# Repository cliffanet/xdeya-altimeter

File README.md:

# Высотомер "Хде-Йа"

Инструмент для парашютиста - гибрид высотомера и Navi-возвращалки.

***
## Возможности

* Классические для высотомера: отображение высоты, логбук и т.д.
* Приём сигнала навигации (GPS + GLONASS)
* Отображение направления и расстояния до заранее сохранённой точки (возвращалка)
* Отображение вертикальной (по барометру) и горизонтальной (по навигации) скоростей
* В логбуке сохраняются показания высотомера и координаты на местности
* Запись трека со всеми имеющимися параметрами барометра и GPS/GLONASS-приёмника
* Взаимодействие с приложением (просмотр логбука, прыжков)

***
## Назначение

* Изначально устройство разрабатывалось как возвращалка в плохих метеоусловиях.

* Студенты, тренирующие точность приземления, смогут на земле разобрать прыжок, имея объективное средство контроля своих перемещений в пространстве.

* Мне как лот организатору групповых прыжков помогало контролировать точку выброски, сильно разгружая голову для остальных функций (взаимодействие с подопечными на борту, дополнительный контроль верности сигналов на выброску), а также помогая объективно оценить задержки выброски из-за неуспевания подготовиться вовремя к отделению.

* Инженеры, программисты микроконтроллеров, использующих Arduino и подобные средства разработки, найдут в этом устройстве полигон для экспериментов в воздухе.

>**Важно:** Устройство не может использоваться для тайного контроля за владельцем, т.к. передача данных вне устройства происходит только по запросу пользователя.

Впрочем, это открытый проект, и каждый может доработать Программное Обеспечение под свои нужды.

***
## Документация

* [Самое краткое руководство](doc/userman/simple/README.md) \[[PDF](doc/userman/xdeya-simple.pdf)|[Word](doc/userman/xdeya-simple.docx)\]
* [Как это сделать?](doc/userman/howdo/README.md) \[[PDF](doc/userman/xdeya-howdo.pdf)|[Word](doc/userman/xdeya-howdo.docx)\]
* [Описание Меню прибора](doc/userman/menu/README.md) \[[PDF](doc/userman/xdeya-menu.pdf)|[Word](doc/userman/xdeya-menu.docx)\]
* [Технические особенности и разъяснения](doc/userman/tech/README.md) \[[PDF](doc/userman/xdeya-tech.pdf)|[Word](doc/userman/xdeya-tech.docx)\]

* [Модификации](doc/models/README.md) - подробное описание аппаратных вариантов и их особенностей с фото.
* [Используемые комплектующие](doc/build/hardware.md)
* [Сколько стоит и где купить](doc/build/price.md)
* [Исходники](doc/code/README.md) - где, что лежит, права на использование, помощь при компиляции.
* [Где скачать](doc/download.md)

***

<video width="475" controls title="demo">
  <source src="doc/demo.mp4" type="video/mp4">
</video>

***
## Контакты

Меня зовут Николай, веду проект `Высотомер + Навигация`. Связаться со мной можно:

* Telegram канал с информацией: [@xdeya](https://t.me/xdeya)
* Telegram: [Cliff](https://t.me/cliffa_net)
* cliff_mail@mail.ru
* Cайт проекта: [xdeya.ru](http://xdeya.ru)

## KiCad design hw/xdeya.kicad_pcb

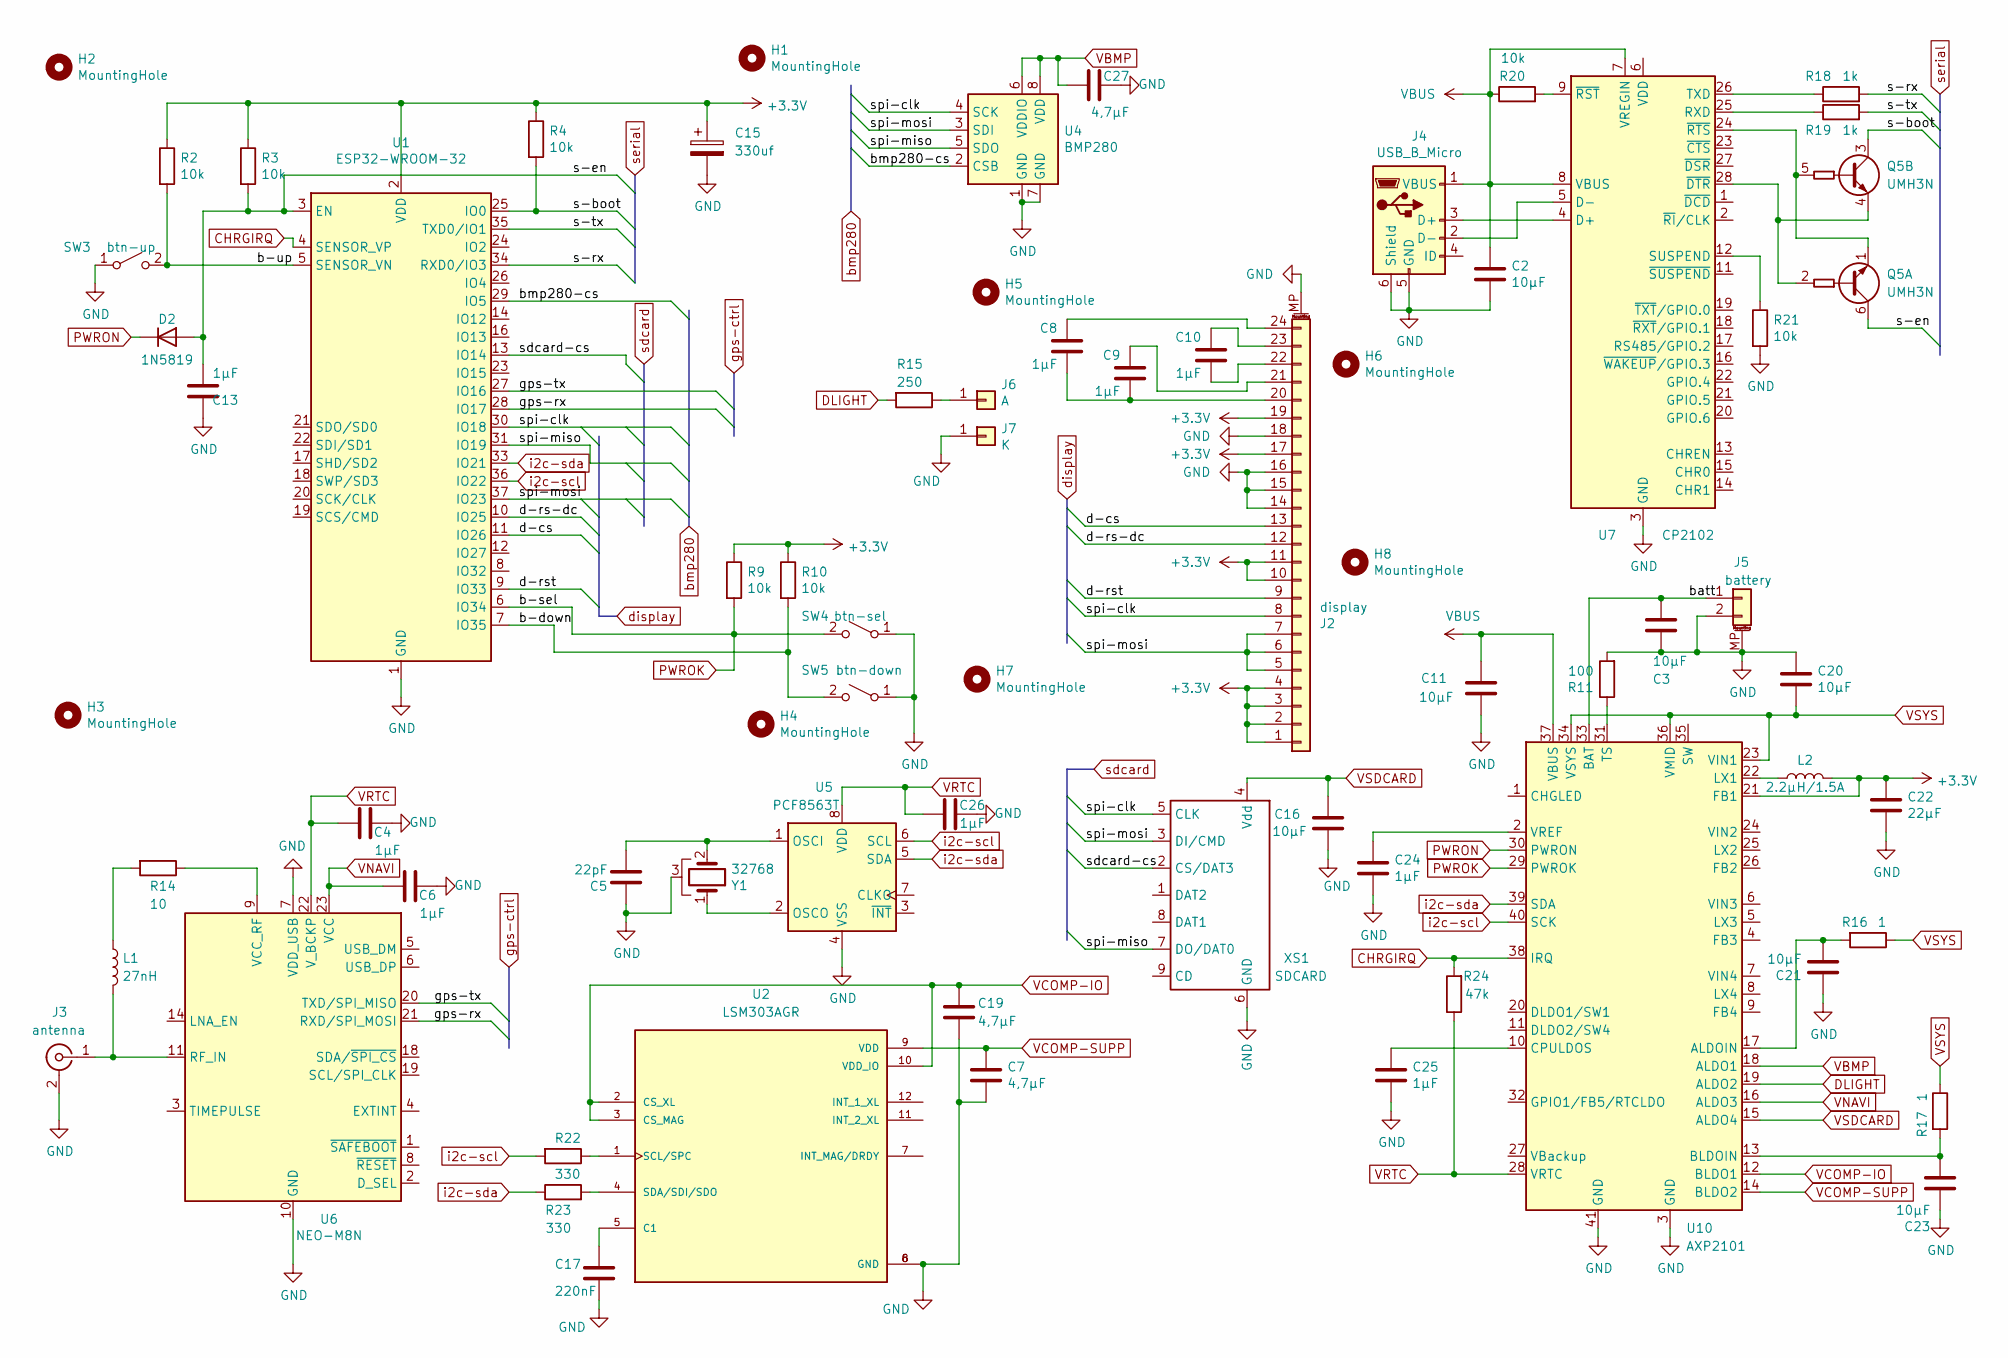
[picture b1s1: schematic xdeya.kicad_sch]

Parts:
C2, C3, C11, C16, C20, C21, C23: 10μF; C_0805_2012Metric
C4, C6, C8, C9, C10, C13, C24, C25, C26: 1μF; C_0805_2012Metric
C5: 22pF; C_0805_2012Metric
C7, C19, C27: 4,7μF; C_0805_2012Metric
C15: 330uf; CP_EIA-7343-20_Kemet-V
C17: 220nF; C_0805_2012Metric
C22: 22μF; C_0805_2012Metric
D2: 1N5819; D_SOD-323
H1, H2, H3, H4: MountingHole; MountingHole_3.2mm_M3
H5, H6: MountingHole; MountingHole_2.2mm_M2
H7, H8: MountingHole; MountingHole_1.5
J2: display; TE_2-1734839-4_1x24-1MP_P0.5mm_Horizontal
J3: antenna; SMA_Molex_73251-2200_Horizontal
J4: USB_B_Micro; USB_Micro-B_Molex-105017-0001
J5: battery; Molex_PicoBlade_53261-0271_1x02-1MP_P1.25mm_Horizontal
J6: A; SolderWire-1sqmm_1x01_D1.4mm_OD2.7mm
J7: K; SolderWire-1sqmm_1x01_D1.4mm_OD2.7mm
L1: 27nH; L_0805_2012Metric
L2: 2.2μH/1.5A; L_Wurth_WE-LQSH-3012
Q5: UMH3N; SOT-363_SC-70-6
R2, R3, R4, R9, R10, R20, R21: 10k; R_0805_2012Metric
R11: 100; R_0805_2012Metric
R14: 10; R_0805_2012Metric
R15: 250; R_0805_2012Metric
R16, R17: 1; R_0805_2012Metric
R18, R19: 1k; R_0805_2012Metric
R22, R23: 330; R_0805_2012Metric
R24: 47k; R_0805_2012Metric
SW3: btn-up; SW_Push_1P1T_NO_6x6mm_H9.5mm
SW4: btn-sel; SW_Push_1P1T_NO_6x6mm_H9.5mm
SW5: btn-down; SW_Push_1P1T_NO_6x6mm_H9.5mm
U1: ESP32-WROOM-32
U2: LSM303AGR; PQFN50P200X200X100-12N; PARTREV 10
U4: BMP280; Bosch_LGA-8_2x2.5mm_P0.65mm_ClockwisePinNumbering
U5: PCF8563T; SOIC-8_3.9x4.9mm_P1.27mm
U6: NEO-M8N; ublox_NEO
U7: CP2102; QFN-28-1EP_5x5mm_P0.5mm_EP3.35x3.35mm
U10: AXP2101; QFN-40-1EP_5x5mm_P0.4mm_EP3.6x3.6mm_ThermalVias
XS1: SDCARD; Conn_uSDcard
Y1: 32768; Crystal_DS26_D2.0mm_L6.0mm_Horizontal_1EP_style2

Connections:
+3.3V: C15.1, C22.1, J2.1, J2.2, J2.3, J2.4, J2.10, J2.11, J2.17, J2.19, L2.2, R2.1, R3.1, R4.1, R9.1, R10.1, U1.2 (VDD), U10.21 (FB1)
/b-down: R10.2, SW5.2 (B), U1.7 (IO35)
/b-up: R2.2, SW3.2 (B), U1.5 (SENSOR_VN)
/batt: C3.1, J5.1, U10.33 (BAT)
/bmp280-cs: U1.29 (IO5), U4.2 (CSB)
/d-cs: J2.13, U1.11 (IO26)
/d-rs-dc: J2.12, U1.10 (IO25)
/d-rst: J2.9, U1.9 (IO33)
/gps-rx: U1.28 (IO17), U6.21 (RXD/SPI_MOSI)
/gps-tx: U1.27 (IO16), U6.20 (TXD/SPI_MISO)
/s-boot: Q5.3 (C2), R4.2, U1.25 (IO0)
/s-en: C13.2, D2.2 (A), Q5.6 (C1), R3.2, U1.3 (EN)
/s-rx: R18.2, U1.34 (RXD0/IO3)
/s-tx: R19.2, U1.35 (TXD0/IO1)
/sdcard-cs: U1.13 (IO14), XS1.2 (CS/DAT3)
/spi-clk: J2.8, U1.30 (IO18), U4.4 (SCK), XS1.5 (CLK)
/spi-miso: U1.31 (IO19), U4.5 (SDO), XS1.7 (DO/DAT0)
/spi-mosi: J2.5, J2.6, J2.7, U1.37 (IO23), U4.3 (SDI), XS1.3 (DI/CMD)
CHRGIRQ: R24.2, U1.4 (SENSOR_VP), U10.38 (IRQ)
DLIGHT: R15.2, U10.19 (ALDO2)
GND: C2.2, C3.2, C4.2, C5.1, C6.2, C7.2, C11.1, C13.1, C15.2, C16.2, C17.2, C19.2, C20.1, C21.1, C22.2, C23.1, C24.2, C25.2, C26.2, C27.2, J2.14, J2.15, J2.16, J2.18, J2.MP (MountPin), J3.2 (Ext), J4.5 (GND), J4.6 (Shield), J5.2, J5.MP (MountPin), J7.1, R11.2, R21.2, SW3.1 (A), SW4.1 (A), SW5.1 (A), U1.1 (GND), U1.15 (GND), U1.38 (GND), U1.39 (GND), U2.6 (GND), U2.8 (GND), U4.1 (GND), U4.7 (GND), U5.4 (VSS), U6.7 (VDD_USB), U6.10 (GND), U6.12 (GND), U6.13 (GND), U6.24 (GND), U7.3 (GND), U7.29 (GND), U10.3 (GND), U10.41 (GND), XS1.6 (GND), Y1.3
unnamed: C8.1, C9.1, J2.20
unnamed: C9.2, J2.21
unnamed: C10.1, J2.22
unnamed: C10.2, J2.23
unnamed: C8.2, J2.24
unnamed: J3.1 (In), L1.2, U6.11 (RF_IN)
unnamed: J4.3 (D+), U7.4 (D+)
unnamed: J4.2 (D-), U7.5 (D-)
unnamed: J6.1, R15.1
unnamed: L1.1, R14.2
unnamed: Q5.2 (B1), Q5.4 (E2), U7.28 (~DTR)
unnamed: Q5.1 (E1), Q5.5 (B2), U7.24 (~RTS)
unnamed: C17.1, U2.5 (C1)
unnamed: R22.1, U2.1 (SCL/SPC)
unnamed: R23.2, U2.4 (SDA/SDI/SDO)
unnamed: C5.2, U5.1 (OSCI), Y1.2
unnamed: U5.2 (OSCO), Y1.1
unnamed: R14.1, U6.9 (VCC_RF)
unnamed: R19.1, U7.25 (RXD)
unnamed: R21.1, U7.12 (SUSPEND)
unnamed: R18.1, U7.26 (TXD)
unnamed: R20.2, U7.9 (~RST)
unnamed: C21.2, R16.2, U10.17 (ALDOIN)
unnamed: C23.2, R17.2, U10.13 (BLDOIN)
unnamed: C25.1, U10.10 (CPULDOS)
unnamed: L2.1, U10.22 (LX1)
unnamed: R11.1, U10.31 (TS)
unnamed: C24.1, U10.2 (VREF)
PWROK: R9.2, SW4.2 (B), U1.6 (IO34), U10.29 (PWROK)
PWRON: D2.1 (K), U10.30 (PWRON)
VBMP: C27.1, U4.6 (VDDIO), U4.8 (VDD), U10.18 (ALDO1)
VBUS: C2.1, C11.2, J4.1 (VBUS), R20.1, U7.7 (VREGIN), U7.8 (VBUS), U10.37 (VBUS)
VCOMP-IO: C19.1, U2.2 (CS_XL), U2.3 (CS_MAG), U2.10 (VDD_IO), U10.12 (BLDO1)
VCOMP-SUPP: C7.1, U2.9 (VDD), U10.14 (BLDO2)
VNAVI: C6.1, U6.23 (VCC), U10.16 (ALDO3)
VRTC: C4.1, C26.1, R24.1, U5.8 (VDD), U6.22 (V_BCKP), U10.28 (VRTC)
VSDCARD: C16.1, U10.15 (ALDO4), XS1.4 (Vdd)
VSYS: C20.2, R16.1, R17.1, U10.23 (VIN1), U10.34 (VSYS), U10.36 (VMID)
i2c-scl: R22.2, U1.36 (IO22), U5.6 (SCL), U10.40 (SCK)
i2c-sda: R23.1, U1.33 (IO21), U5.5 (SDA), U10.39 (SDA)

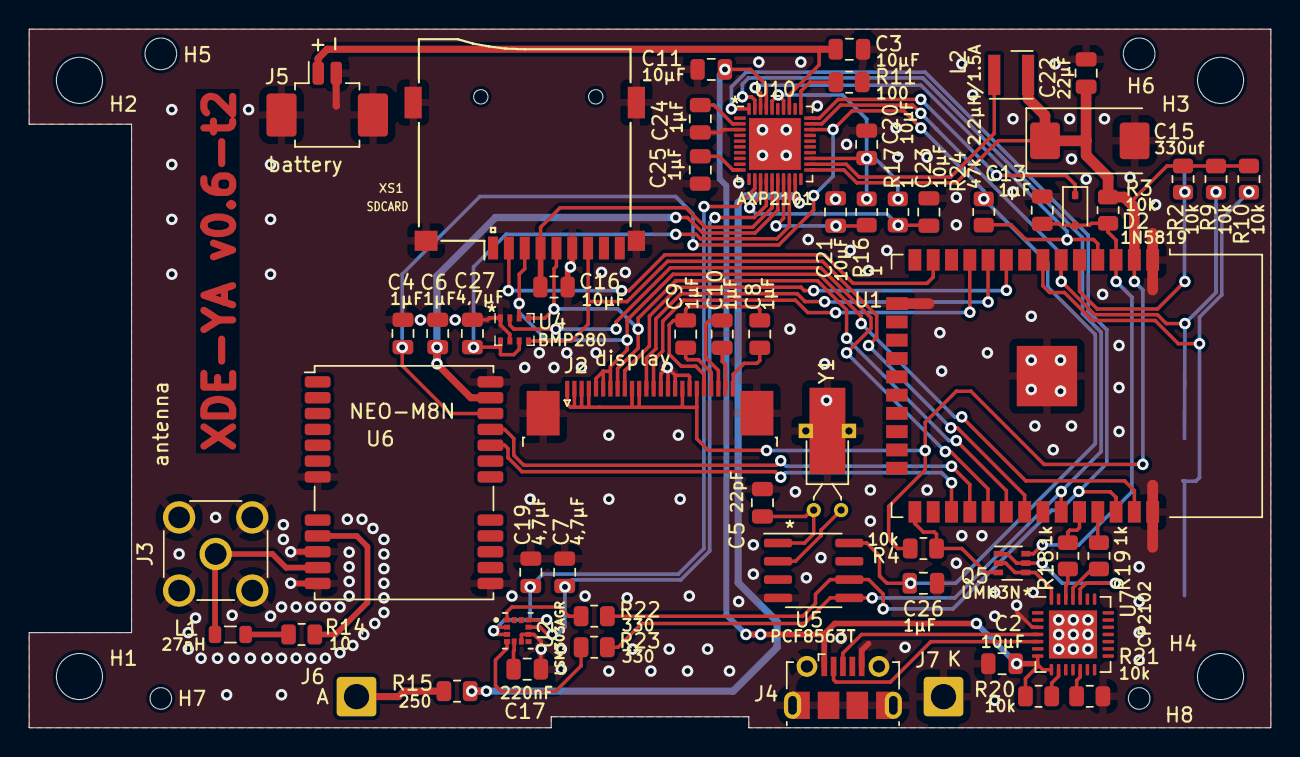
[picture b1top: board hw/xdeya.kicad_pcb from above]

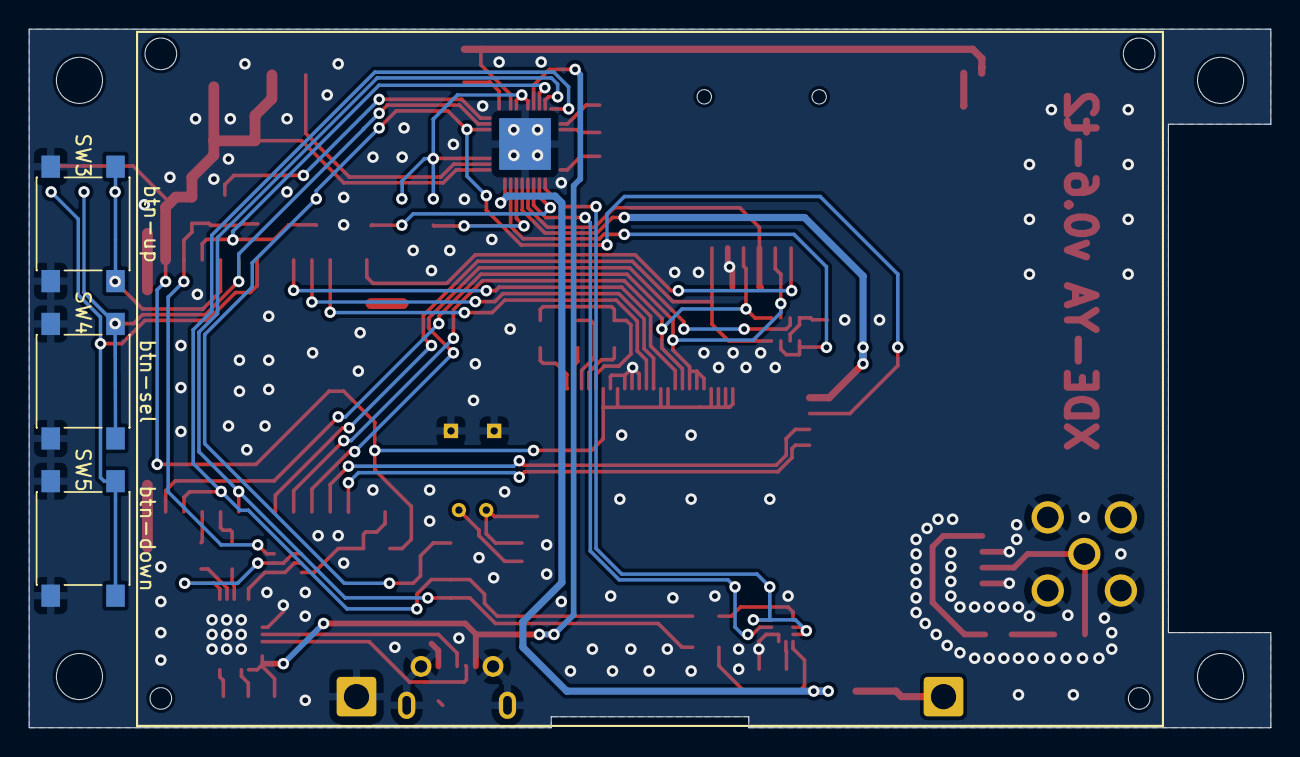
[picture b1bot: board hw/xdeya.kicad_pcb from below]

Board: 2 copper layers, 86.2 x 48.5 mm, 70 parts (3 on the bottom side), 61 nets.

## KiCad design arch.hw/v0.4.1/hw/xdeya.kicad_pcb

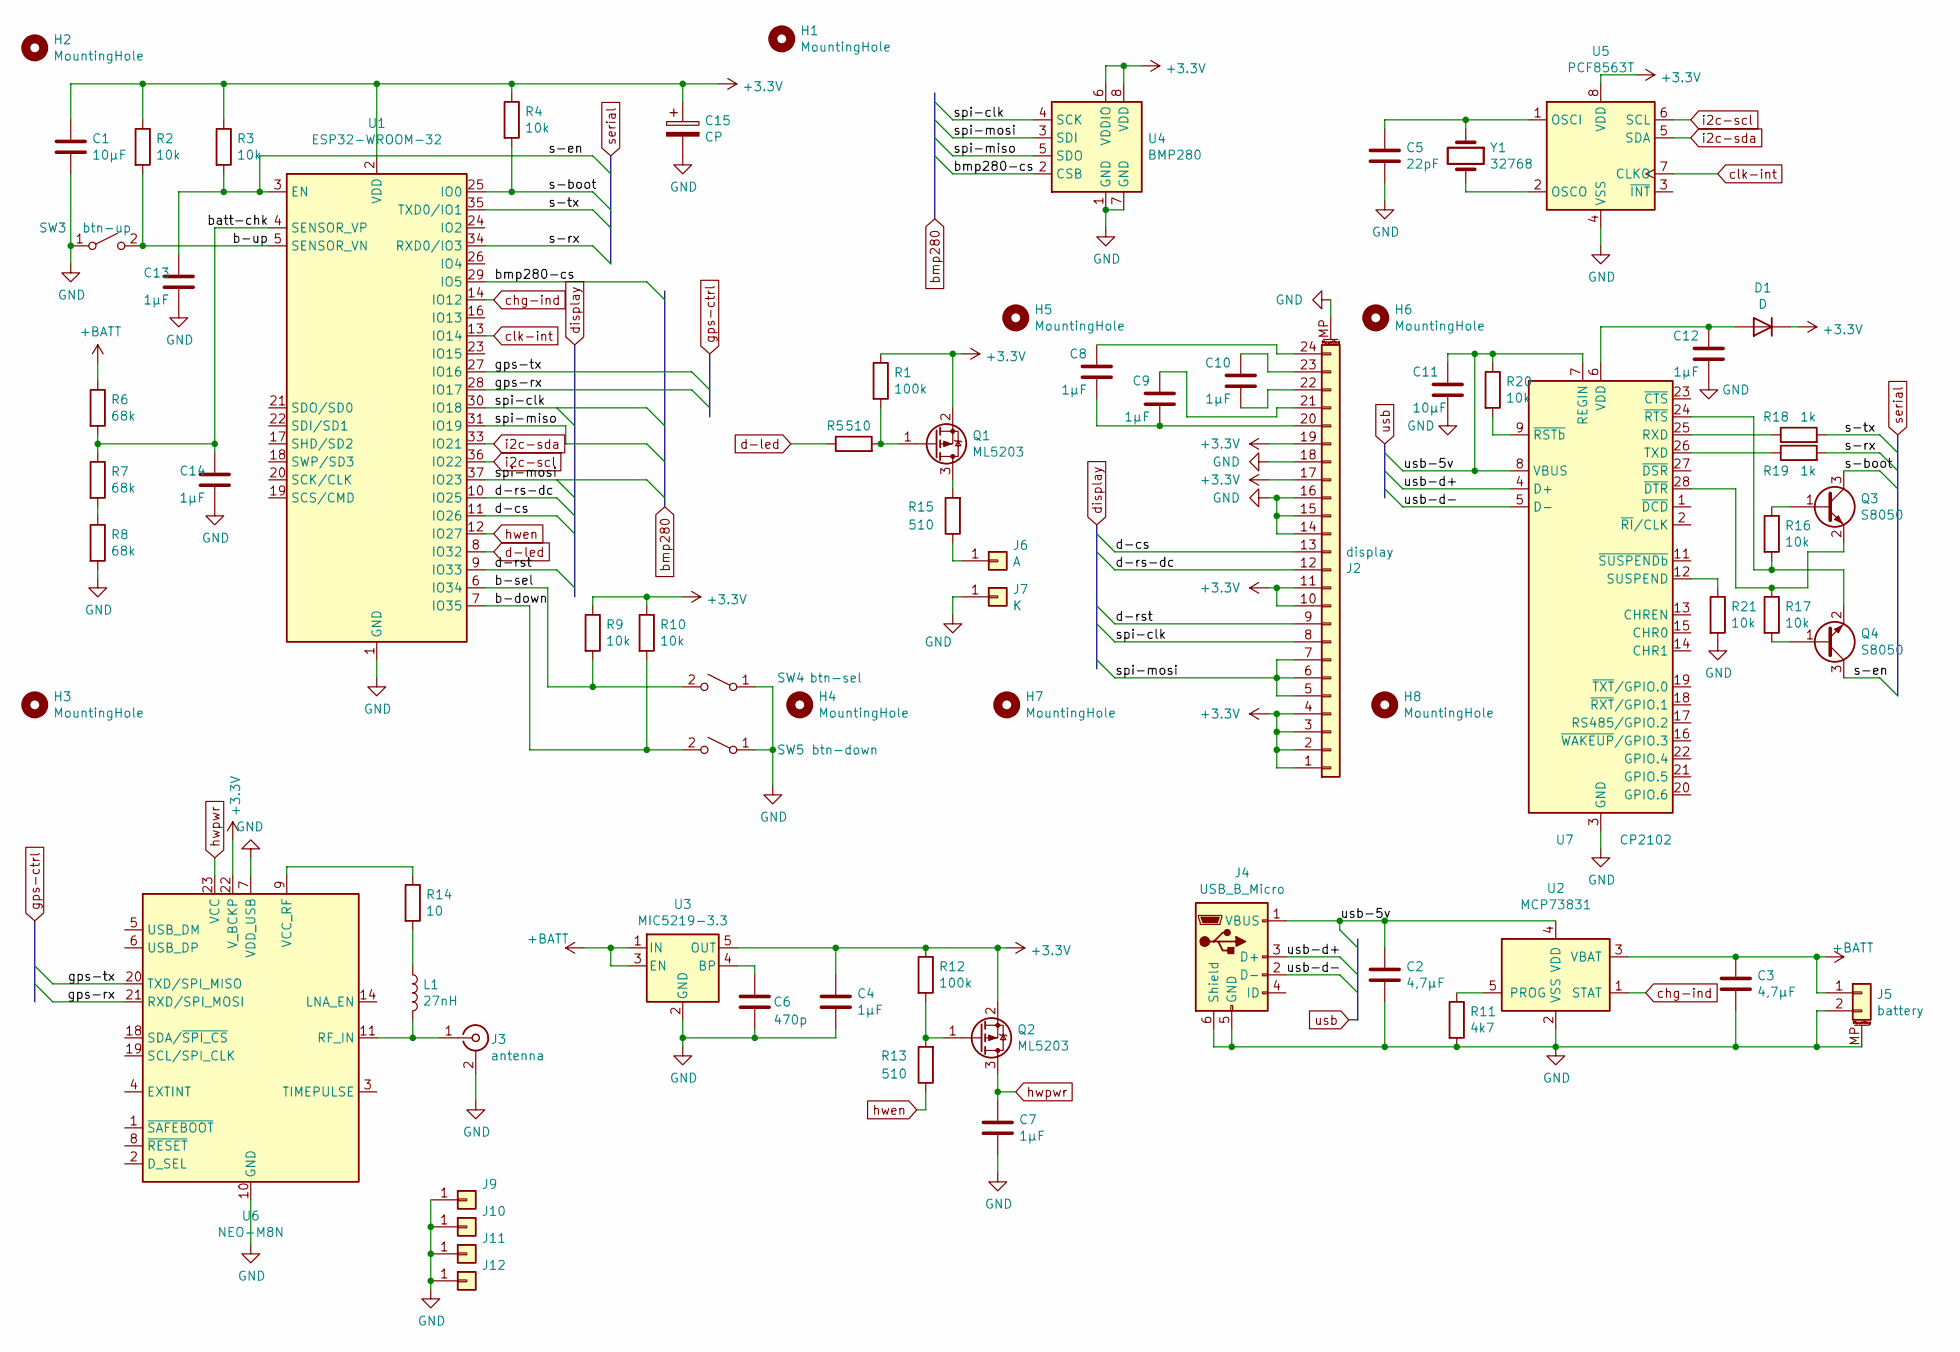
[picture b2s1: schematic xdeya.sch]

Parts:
C1, C11: 10μF; C_0805_2012Metric
C2, C3: 4,7μF; C_0805_2012Metric
C4, C7, C8, C9, C10, C12, C13, C14: 1μF; C_0805_2012Metric
C5: 22pF; C_0805_2012Metric
C6: 470p; C_0805_2012Metric
C15: CP; CP_Radial_D4.0mm_P1.50mm
D1: D; D_0805_2012Metric
H1, H2, H3, H4: MountingHole; MountingHole_3.2mm_M3
H5, H6: MountingHole; MountingHole_2.2mm_M2
H7, H8: MountingHole; MountingHole_1.5
J2: display; TE_2-1734839-4_1x24-1MP_P0.5mm_Horizontal
J3: antenna; U.FL_Molex_MCRF_73412-0110_Vertical
J4: USB_B_Micro; USB_Micro-B_Molex-105017-0001
J5: battery; Molex_PicoBlade_53261-0271_1x02-1MP_P1.25mm_Horizontal
J6: A; SolderWire-1sqmm_1x01_D1.4mm_OD2.7mm
J7: K; SolderWire-1sqmm_1x01_D1.4mm_OD2.7mm
J9, J10, J11, J12: A; SolderWirePad_1x01_SMD_3x6mm
L1: 27nH; L_0805_2012Metric
Q1, Q2: ML5203; SOT-23
Q3, Q4: S8050; SOT-23
R1, R12: 100k; R_0805_2012Metric
R2, R3, R4, R9, R10, R16, R17, R20, R21: 10k; R_0805_2012Metric
R5, R13, R15: 510; R_0805_2012Metric
R6, R7, R8: 68k; R_0805_2012Metric
R11: 4k7; R_0805_2012Metric
R14: 10; R_0805_2012Metric
R18, R19: 1k; R_0805_2012Metric
SW3: btn-up; SW_Push_1P1T_NO_6x6mm_H9.5mm
SW4: btn-sel; SW_Push_1P1T_NO_6x6mm_H9.5mm
SW5: btn-down; SW_Push_1P1T_NO_6x6mm_H9.5mm
U1: ESP32-WROOM-32
U2: MCP73831; SOT-23-5
U3: MIC5219-3.3; SOT-23-5
U4: BMP280; Bosch_LGA-8_2x2.5mm_P0.65mm_ClockwisePinNumbering
U5: PCF8563T; SOIC-8_3.9x4.9mm_P1.27mm
U6: NEO-M8N; ublox_NEO
U7: CP2102; QFN-28-1EP_5x5mm_P0.5mm_EP3.35x3.35mm
Y1: 32768; Crystal_AT310_D3.0mm_L10.0mm_Vertical

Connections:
+3V3: C1.1, C4.1, C15.1, D1.1 (K), J2.1, J2.2, J2.3, J2.4, J2.10, J2.11, J2.17, J2.19, Q1.2 (S), Q2.2 (S), R1.1, R2.1, R3.1, R4.1, R9.1, R10.1, R12.1, U1.2 (VDD), U3.5 (OUT), U4.6 (VDDIO), U4.8 (VDD), U5.8 (VDD), U6.22 (V_BCKP)
+BATT: C3.1, J5.1, R6.1, U2.3 (VBAT), U3.1 (IN), U3.3 (EN)
/b-down: R10.2, SW5.2 (B), U1.7 (IO35)
/b-sel: R9.2, SW4.2 (B), U1.6 (IO34)
/b-up: R2.2, SW3.2 (B), U1.5 (SENSOR_VN)
/batt-chk: C14.1, R6.2, R7.1, U1.4 (SENSOR_VP)
/bmp280-cs: U1.29 (IO5), U4.2 (CSB)
/d-cs: J2.13, U1.11 (IO26)
/d-rs-dc: J2.12, U1.10 (IO25)
/d-rst: J2.9, U1.9 (IO33)
/gps-rx: U1.28 (IO17), U6.21 (RXD/SPI_MOSI)
/gps-tx: U1.27 (IO16), U6.20 (TXD/SPI_MISO)
/s-boot: Q3.3 (C), R4.2, U1.25 (IO0)
/s-en: C13.1, Q4.3 (C), R3.2, U1.3 (EN)
/s-rx: R19.2, U1.34 (RXD0/IO3)
/s-tx: R18.2, U1.35 (TXD0/IO1)
/spi-clk: J2.8, U1.30 (IO18), U4.4 (SCK)
/spi-miso: U1.31 (IO19), U4.5 (SDO)
/spi-mosi: J2.5, J2.6, J2.7, U1.37 (IO23), U4.3 (SDI)
/usb-5v: C2.1, C11.1, J4.1 (VBUS), R20.1, U2.4 (VDD), U7.7 (REGIN), U7.8 (VBUS)
/usb-d+: J4.3 (D+), U7.4 (D+)
/usb-d-: J4.2 (D-), U7.5 (D-)
GND: C1.2, C2.2, C3.2, C4.2, C5.2, C6.2, C7.2, C11.2, C12.1, C13.2, C14.2, C15.2, J2.14, J2.15, J2.16, J2.18, J2.MP (MountPin), J3.2 (Ext), J4.5 (GND), J4.6 (Shield), J5.2, J5.MP (MountPin), J7.1, J9.1, J10.1, J11.1, J12.1, R8.2, R11.2, R21.2, SW3.1 (A), SW4.1 (A), SW5.1 (A), U1.1 (GND), U1.15 (GND), U1.38 (GND), U1.39 (GND), U2.2 (VSS), U3.2 (GND), U4.1 (GND), U4.7 (GND), U5.4 (VSS), U6.7 (VDD_USB), U6.10 (GND), U6.12 (GND), U6.13 (GND), U6.24 (GND), U7.3 (GND), U7.29 (GND)
unnamed: C5.1, U5.1 (OSCI), Y1.1
unnamed: C6.1, U3.4 (BP)
unnamed: C8.1, C9.1, J2.20
unnamed: C8.2, J2.24
unnamed: C9.2, J2.21
unnamed: C10.1, J2.22
unnamed: C10.2, J2.23
unnamed: C12.2, D1.2 (A), U7.6 (VDD)
unnamed: J3.1 (In), L1.2, U6.11 (RF_IN)
unnamed: J6.1, R15.1
unnamed: L1.1, R14.2
unnamed: Q1.1 (G), R1.2, R5.2
unnamed: Q1.3 (D), R15.2
unnamed: Q2.1 (G), R12.2, R13.2
unnamed: Q3.1 (B), R16.1
unnamed: Q3.2 (E), R17.1, U7.28 (~DTR)
unnamed: Q4.1 (B), R17.2
unnamed: Q4.2 (E), R16.2, U7.24 (~RTS)
unnamed: R7.2, R8.1
unnamed: R11.1, U2.5 (PROG)
unnamed: R14.1, U6.9 (VCC_RF)
unnamed: R18.1, U7.25 (RXD)
unnamed: R19.1, U7.26 (TXD)
unnamed: R20.2, U7.9 (~RSTb)
unnamed: R21.1, U7.12 (SUSPEND)
unnamed: U5.2 (OSCO), Y1.2
chg-ind: U1.14 (IO12), U2.1 (STAT)
clk-int: U1.13 (IO14), U5.7 (CLKO)
d-led: R5.1, U1.8 (IO32)
hwen: R13.1, U1.12 (IO27)
hwpwr: C7.1, Q2.3 (D), U6.23 (VCC)
i2c-scl: U1.36 (IO22), U5.6 (SCL)
i2c-sda: U1.33 (IO21), U5.5 (SDA)

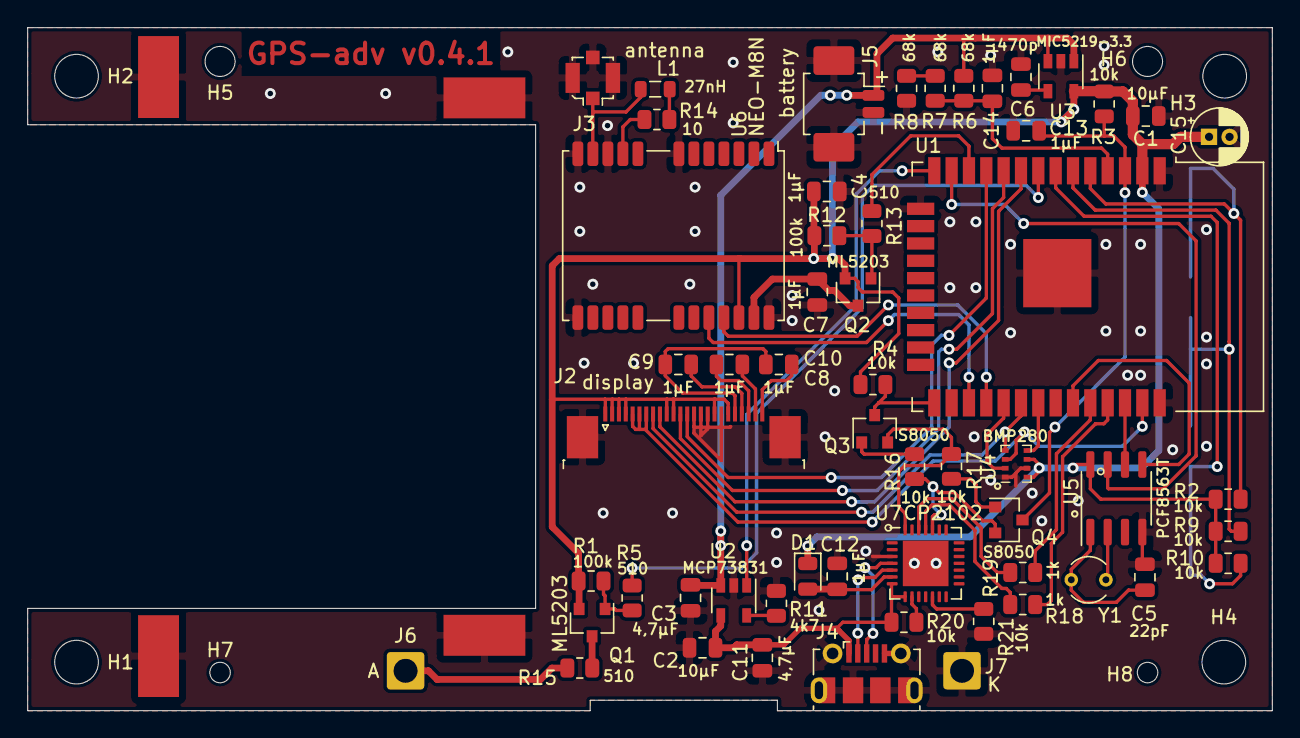
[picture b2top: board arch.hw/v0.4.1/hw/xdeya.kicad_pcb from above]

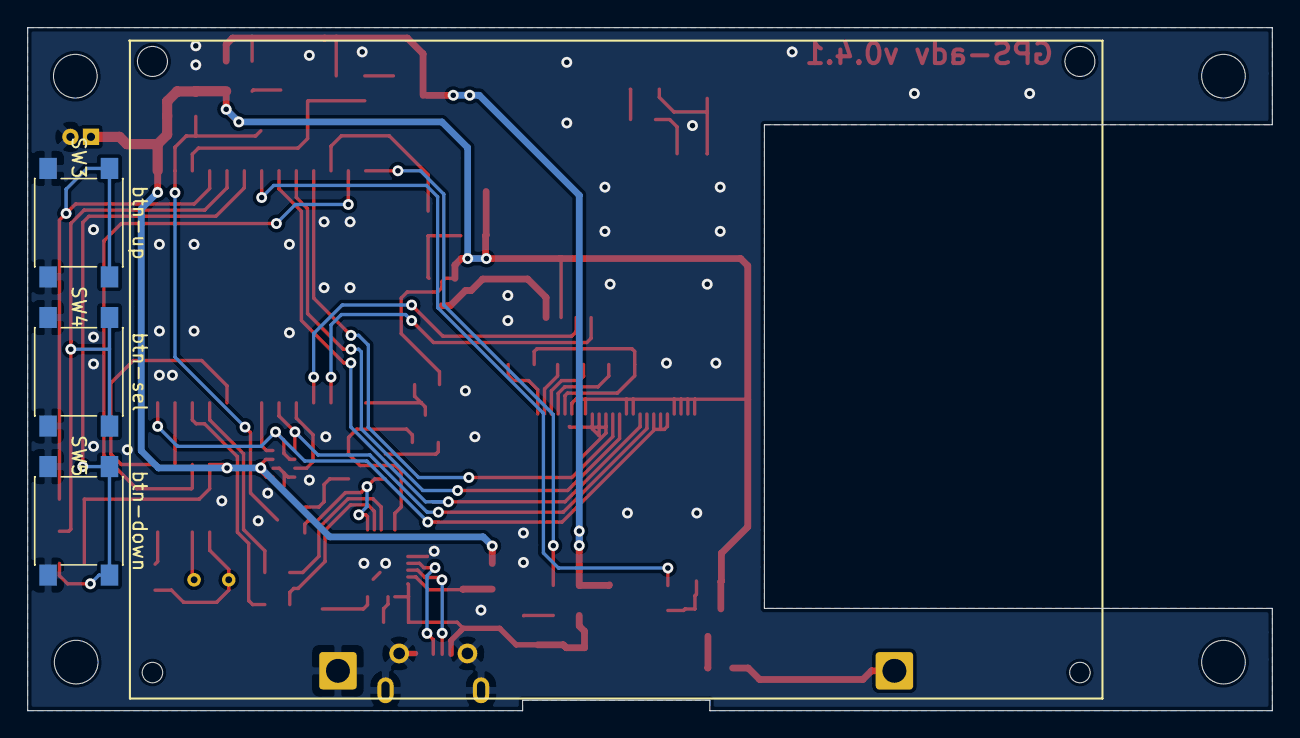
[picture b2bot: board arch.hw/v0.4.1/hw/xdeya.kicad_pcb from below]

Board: 2 copper layers, 91.2 x 50.0 mm, 71 parts (3 on the bottom side), 56 nets.

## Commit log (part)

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2021-09-26 питание - проработка режима "сон" - выход по нажатию средней кнопки или при начале подъёма
2021-09-28 box - поправлено отверстие под экран, отверстие под usb, добавлена версия с креплением шнуром
2021-09-30 доработано управление питанием в sleep и pwroff режимах и инициализация после них
2021-10-01 при синхронизации отключать bitsync у часов (освободить пин-12)
2021-10-01 на время старта вифи отключать ватчдог по питанию
2021-10-01 при напряжении на батарее ниже N не включать высотник, а моргать батареей и выключаться
2021-10-03 мелкие доработки
2021-10-14 поправлены частоты спящего режима
2021-10-14 дебаг при старте вифи - почему-то иногда на этом этапе возникает паника
2021-10-14 поправлены таймауты при работе с вифи (осталось после переезда c millis() на потактовое измерение времени)
2021-10-15 переделка протокола хранения записей в файле: длина (2 байта), данные, chksum (2 байта, как в ublox)
2021-10-16 логбук - запоминать время взлёта ла
2021-10-16 синхронизация - если данных отправилось меньше, чем надо, делать ещё несколько попыток
2021-10-16 калибровка значения напряжения на батарее
2021-10-20 бага инициализации жпс модема
2021-10-22 arch.hw, hw, box - поправлены имена файлов
2021-10-28 настройки управления питанием - параметры в конфиге, пункты меню
2021-10-29 автоматически включать трек на заданной высоте в подъёме
2021-11-01 управление функциями кнопок (верх/низ)
2021-11-05 руссификация - обвязка, menustatic
2021-11-06 руссификация - поправлены баги длины строки для utf
2021-11-06 из не-debug версии убрана debug-страница
2021-11-07 altcalc - добавлен алгоритм отслеживания фаз прыжка, надо тестировать и применять в jump/proc
2021-11-08 обновлённая версия esp32 sdk
2021-11-09 пересмотр кода подключения по wifi
2021-11-11 wifi - проблема бага повторной синхронизации была в используемой обвязке sdk v.2.0.1. После отката на v.2.0.0 (release) проблема ушла, и так же перестал сбоить passive режим.
2021-11-12 документация - наброски заголовочного раздела
2021-11-13 документация - руководство пользователя - структура главного меню и описание GPS-точек
2021-11-13 документация - руководство пользователя - меню - Система
2021-11-14 документация - руководство пользователя - меню - Параметры
2021-11-14 документация - руководство пользователя - доделан Высотомер
2021-11-16 документация - руководство пользователя - Автоматические операции
2021-11-18 документация - руководство пользователя - Синхронизация и Обновление ПО
2021-11-18 документация - руководство пользователя - Главные экраны и Первое знакомство (каркас)
2021-11-19 документация - скрипт генерации pdf и doc из md
2021-11-20 документация - Ссылки на руководство пользователя в разных форматах
2021-11-21 документация - доделки в Текущих проблемах
2021-11-21 документация - небольшие доработки и заготовки
2021-11-24 документация - немного ссылок
2021-11-25 документация - аналитика общая - стилистика
2021-11-26 документация - описание и фото модификаций, доработка антенны
2021-11-26 документация - фото монтажа
2021-11-28 документация - доработка "руководства" - Первое знакомство и Главные экраны
2021-11-28 документация - доработка "руководства" - обновлены pdf/docx
2021-12-04 hw - тестовый вариант с антенным усилителем
2022-01-25 страница через настройки - "все видимые спутники"
2022-01-26 gps - дебаг в консоль конфига используемых gnss-систем
2022-01-29 компас - отрисовка точки и направления движения - надо проверять
2022-01-30 компас - переделана под новый формат отображения старая страница с высотомером
2022-01-30 опция в настройках "использовать компас"
2022-01-30 компас - небольшие корректировки коэфициентов
2022-02-05 добавлена библиотека filtlib, компас - усреднение угла через FilterAvgDeg
2022-02-19 обновлена библиотека filtlib
2022-02-20 рефакторинг работы с файлами - wifi-пароли
2022-02-25 компас - вынесены в отдельный модуль: mpu6050/hmc5883, mpu9250(так и не нашёлся магнетометр), lsm303dlh
2022-03-07 документация - доработки
2022-03-07 документация - удлинённый вариант v.0.4
2022-03-07 navi/proc/init - переделка ожидания подтверждения команд и переключения скорости соединения
2022-03-10 filebin, сохранение конфига через класс FileBin
2022-03-10 file - убрано промежуточное звено со ссылкой на fs::File через set-объект
2022-03-12 filebinnum, logbook - передача по сети
2022-03-13 запись трека - через worker и кольцевой курсор (ringcursor) для prelog
2022-03-13 удалён старый модуль по работе с файлами
2022-03-13 баг удаления файлов
2022-03-13 выключение компаса при выключении питания
2022-03-15 удлинённый корпус под v.0.4
2022-03-26 перенос wifi-синхр в worker - подключение к wifi и к серверу
2022-03-26 wifisync/binproto - BinProto (общий класс для набора шаблонов упаковки/распаковки) и BinProtoSend (отдельный класс для отправки)
2022-03-31 binproto - реализация send/pack через упакованную структуру данных (вместо отдельных аргументов)
2022-04-02 binproto - переделана структура наследования классов - отправка теперь происходит без предварительной регистрации команды через прямое указание pk при отправке
2022-04-03 wifisync - отправка точек, логбука и завершение передачи на сервер
2022-04-08 баг списка спутников при большом кол-ве - увеличен размер буфера ubloxproto, добавлен дебаг об объёме принимаемых данных
2022-04-09 выключение барометра при отключении питания, уменьшение времени нажатия для включения питания
2022-04-11 калибровка магнетометра
2022-04-20 hw - v0.5
2022-05-17 корпус - доработка отверстия под SD-карту
2022-05-27 hw0.5 - ориентация компаса
2022-06-02 корпус - поправлены отверстия для кнопок
2022-06-03 писать трек на внутреннюю память, если не смог открыть sd-карту
2022-06-06 документация - обновление прошивки с sd-карты
2022-06-12 корпус - для варианта с лентами на руку уменьшена глубина (теперь такая же, как у варианта со шнуром на ногу)
2022-06-12 navi - подправлена скорость передачи данных
2022-06-13 переделана калибровка компаса
2022-06-13 обработка ошибок компаса (overflow)
2022-09-22 box - по длинной стороне сделан жолоб для более стабильного сочленения сторон
2022-10-09 корректировка индикации заряда аккума, надо тестить
2022-10-09 нави опционально - gps, glonass, gps+glonnas (по умолчанию)
2022-10-09 несколько переименований в коде: GPS -> NAV
2022-10-10 в выкл состоянии при зарядке и коротком нажатии на кнопку - показывать уровень заряда
2022-10-11 переделываем воркер - Navi
2022-10-13 переделываем воркер - вырезали старый функционал
2022-10-13 wifisync - начало новой попытки переделать через воркер и новый сетевой стек
2022-10-16 wifisync - binproto рефакторинг + у воркеров добавлен статус "finished"
2022-10-16 wifisync - получение данных подпроцессом - wifi-пароли
2022-10-16 wifisync - обновление прошивки
2022-10-18 wifisync - доработка отправки списка треков (заголовки) - доведены классы FileBinNum и FileTrack
2022-10-21 wifisync - поправлены баги
2022-10-21 перенумерование треков перед началом записи через отдельный воркер
2022-10-23 box - поправлен жолоб между частями корпуса
2022-10-31 приложение - доработано до момента самого подключения
2022-11-03 поиск устройств по wifi каналу (bt пока откладывается)
2022-11-06 связка с приложением - авторизация
2022-11-06 связка с приложением - получение логбука (только сам список - крайние 50 прыгов)
2022-11-10 связка с приложением - вывод списка треков, привязанных к прыгу, переход на страницу с треком (пока пустая)
2022-11-12 приложение - работа с треком вынесена в отдельный класс
2022-11-13 приложение - доработки отображени трека. Но тут выяснилось, что QWebEngine не работает под мобильными приложениями, поэтому сейчас будем решать эту проблему.
2022-11-18 приложение - начали переделывать окно в qml (движок останется на c++)
2022-11-20 приложение - qml - подключение и авторизация
2022-11-20 приложение - qml - отображение трека
2022-11-24 баг при синхронизации, если логбук пуст
2022-11-25 приложение - переделана генерация трека на карте, сделано отображение подсказок
2022-11-26 приложение - список всех треков
2022-11-28 приложение - доработки под qt 5.15
2022-11-29 баги после чистки
2022-12-25 небольшие доработки
2023-01-24 отображение качества
2023-01-24 новый воркер - переделан trkRotate (возвращаемое значение, немного костыльно)
2023-01-29 при переходе в режим прыжка и в режим пилотирования - не сохранять состояние, чтобы не подлипало
2023-02-06 сюда перенесено приложение на flutter, а исходники приложения на qt удалены
2023-02-11 bt - доработки, но пока запустить так и не удалось: получилось отобразить при поиске устройств в маке, но во flutter почему-то ни один bluetooth модуль не работает.
2023-02-12 app - если нет ошибки и операции - отображать название текущей страницы
2023-02-13 app - автореконнект + авто-авторизация
2023-02-17 app - экспорт трека в gpx
2023-02-18 worker - переделаны: wifisync и sendlogbook
2023-02-18 worker - переделаны: recvwifipass, recvveravail, recvfirmware
2023-02-18 netsync - описание команд протокола передачи
2023-02-19 backup - восстановление нужных файлов из локальной папки на устройство
2023-02-24 app - доработки сетевого процесса: коннект/дисконнект
2023-02-24 документация - в отдельный документ вынесено: Самое краткое руководство
2023-02-24 документация - в отдельный документ вынесено: Технические особенности
2023-02-24 документация - в отдельный документ вынесено: Как это сделать
2023-02-25 документация - hw v.0.5
2023-02-25 документация - описание главных экранов
2023-02-25 документация - картинка с приложением
2023-02-25 документация - favicon и logo
2023-02-26 документация - скачивание файлов
2023-02-26 документация - сайт проекта
2023-02-26 navi - небольшой костыль против бага с нулевыми координатами
2023-02-28 расширенное меню подключения приложения по wifi
2023-03-06 app - непрозрачный фон у иконки
2023-03-08 рефакторинг меню - убрано кеширование строк
2023-03-08 рефакторинг меню - теперь полностью динамическое (new/delete) без статических объектов
2023-03-09 рефакторинг меню - обновление прошивки с SD-карты переделано в воркер + view для просмотра прогресса выполнения
2023-03-10 список треков - пропускать трек, у которого не прочитать заголовок
2023-03-11 app рефакторинг netproc - вынос отдельно списка треков
2023-03-12 app рефакторинг netproc - вынос отдельно wifipass
2023-03-12 app рефакторинг netproc - вынос отдельно files
2023-03-15 app - trkdata - при загрузке формируется параллельный список, разбитый на сегменты; рефакторинг экспорта треков через список, разбитый на сегменты
2023-03-26 баг тестового входа и загрузки трека
2023-04-01 3d трек - информация о точке
2023-04-02 баги hw4
2023-04-02 доработки иконки приложения
2023-04-09 doc - demo video size
2023-04-10 баг ublox-direct-режима у prod-прошивки
2023-04-11 wifi-пароль "по умолчанию" (для точек доступа, которые не умеют быть без пароля)
2023-04-16 вифи синхр - если ип сохраняется, то сохранять и порт подключения
2023-04-16 экран "путь" - автовыбор масштаба, отображение трека, отладочная информация
2023-04-17 экран "путь" - указатель направления движения
2023-04-20 инфо о треке - рядом со временем отображать номер записи в треке
2023-04-23 app - переделано вращение трека
2023-05-01 открытие папки с файлами - пока только список прыжков
2023-05-01 app - график изменения высоты
2023-05-06 кол-во спутников мал цифрами в левом нижнем углу на всех страницах
2023-05-07 drawAlt вынесено в отдельный метод
2023-05-09 опциональное включение приёма всех вариантов спутников
2023-05-14 дебаг страница с отладкой высоты
2023-05-15 doc - download version
2023-06-26 опциональное отключение точности жпс как факта работы жпс
2023-08-09 поправлен профайл начала прыжка + отладка sqdiff
2023-09-02 hw - схема с использованием axp2101
2023-09-05 hw - доделана трассировка платы, но скорее всего, придётся всё переделывать, слишком много пересечений
2023-09-08 hw - поправлены ошибки
2023-09-29 hw - мелкие доработки
2023-10-03 app - баг ссылки сохранения в gpx
2023-10-05 документация - включение/выключение и режим сна
